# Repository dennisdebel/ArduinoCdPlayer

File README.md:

# Arduino CD player

Using an Arduino Pro-mini and an IDE CD-ROM drive to create a standalone CD player.
Based on the [ATAPIDUINO](http://singlevalve.web.fc2.com/Atapiduino/atapiduino.htm) project - code for this in the `original` folder.

For more details, see project on [hackaday.io](https://hackaday.io/project/176545-arduino-cd-player).

# To do
* Add opamp buffer after DAC to protect the output (from accidental plugging in other outputs).

# Supported IDE CD-ROM drives
Sources from [ATAPIDUINO](http://singlevalve.web.fc2.com/Atapiduino/atapiduino.htm) and [ArduinoCdPlayer](https://hackaday.io/project/176545-arduino-cd-player) and [here](https://hackaday.io/project/24905-using-old-cd-drive-as-a-music-player):

## Testing
* AOpen CRW5224 (2003)

## Compatible drives
* AZTECH CDA66801I (1995)
* BTC F563E (2001)
* CREATIVE CD5233E (?) (Starts PLAY instead of remaining paused when NEXT/PREV is used on stopped unit)
* HITACHI CDR-8130 (1997)
* HITACHI CDR-8230 (1997)
* LG CRD-8320B (1998)
* LG CRD-8322B (1999)
* LG CRD-8521B (2001)
* LG GCE-8527B (2005)
* LITE-ON LTN-403L (2000)
* LITE-ON LTN486S (2001)
* NEC CDR 1800A (1997)
* NEC DV-5800A (2001) ("DVD-ROM READER")
* SAMSUNG SC-148C (2001)
* SONY CDU5211 (2001)
* TEAC CD-532E (2000)
* TEAC CD-540E (2001)
* Ultima Electronics CHA-50 (????)

## Non Compatible or possible defect Units
* Compaq CRC#D-8241B (1998) (erratic, defect?)
* Compaq CR-588 (1998) (erratic, defect?)
* H.L Datastorage GCR-8481B (2002) (fails init proc.)
* LG DVD-ROM Drive GDR-H30N (2007) (fails init proc.)
* Philips DVDROM DROM6116/34 (2004) (Only reads TOC sometimes)
* Toshiba XM-6402B (1999) (fails init proc.)

# References
* https://hackaday.io/project/176545-arduino-cd-player
* https://hackaday.io/project/24905-using-old-cd-drive-as-a-music-player
* http://singlevalve.web.fc2.com/Atapiduino/atapiduino.htm 
* https://github.com/lmiori92/AtapiduinoSingleChip
* productized version of similar idea: [CD-ROM DVD-ROM IDE ROM Audio Player controller DIY kit ROM to Turntable](https://www.ebay.co.uk/itm/CD-ROM-DVD-ROM-IDE-ROM-Audio-Player-controller-DIY-kit-ROM-to-Turntable/324207457799)

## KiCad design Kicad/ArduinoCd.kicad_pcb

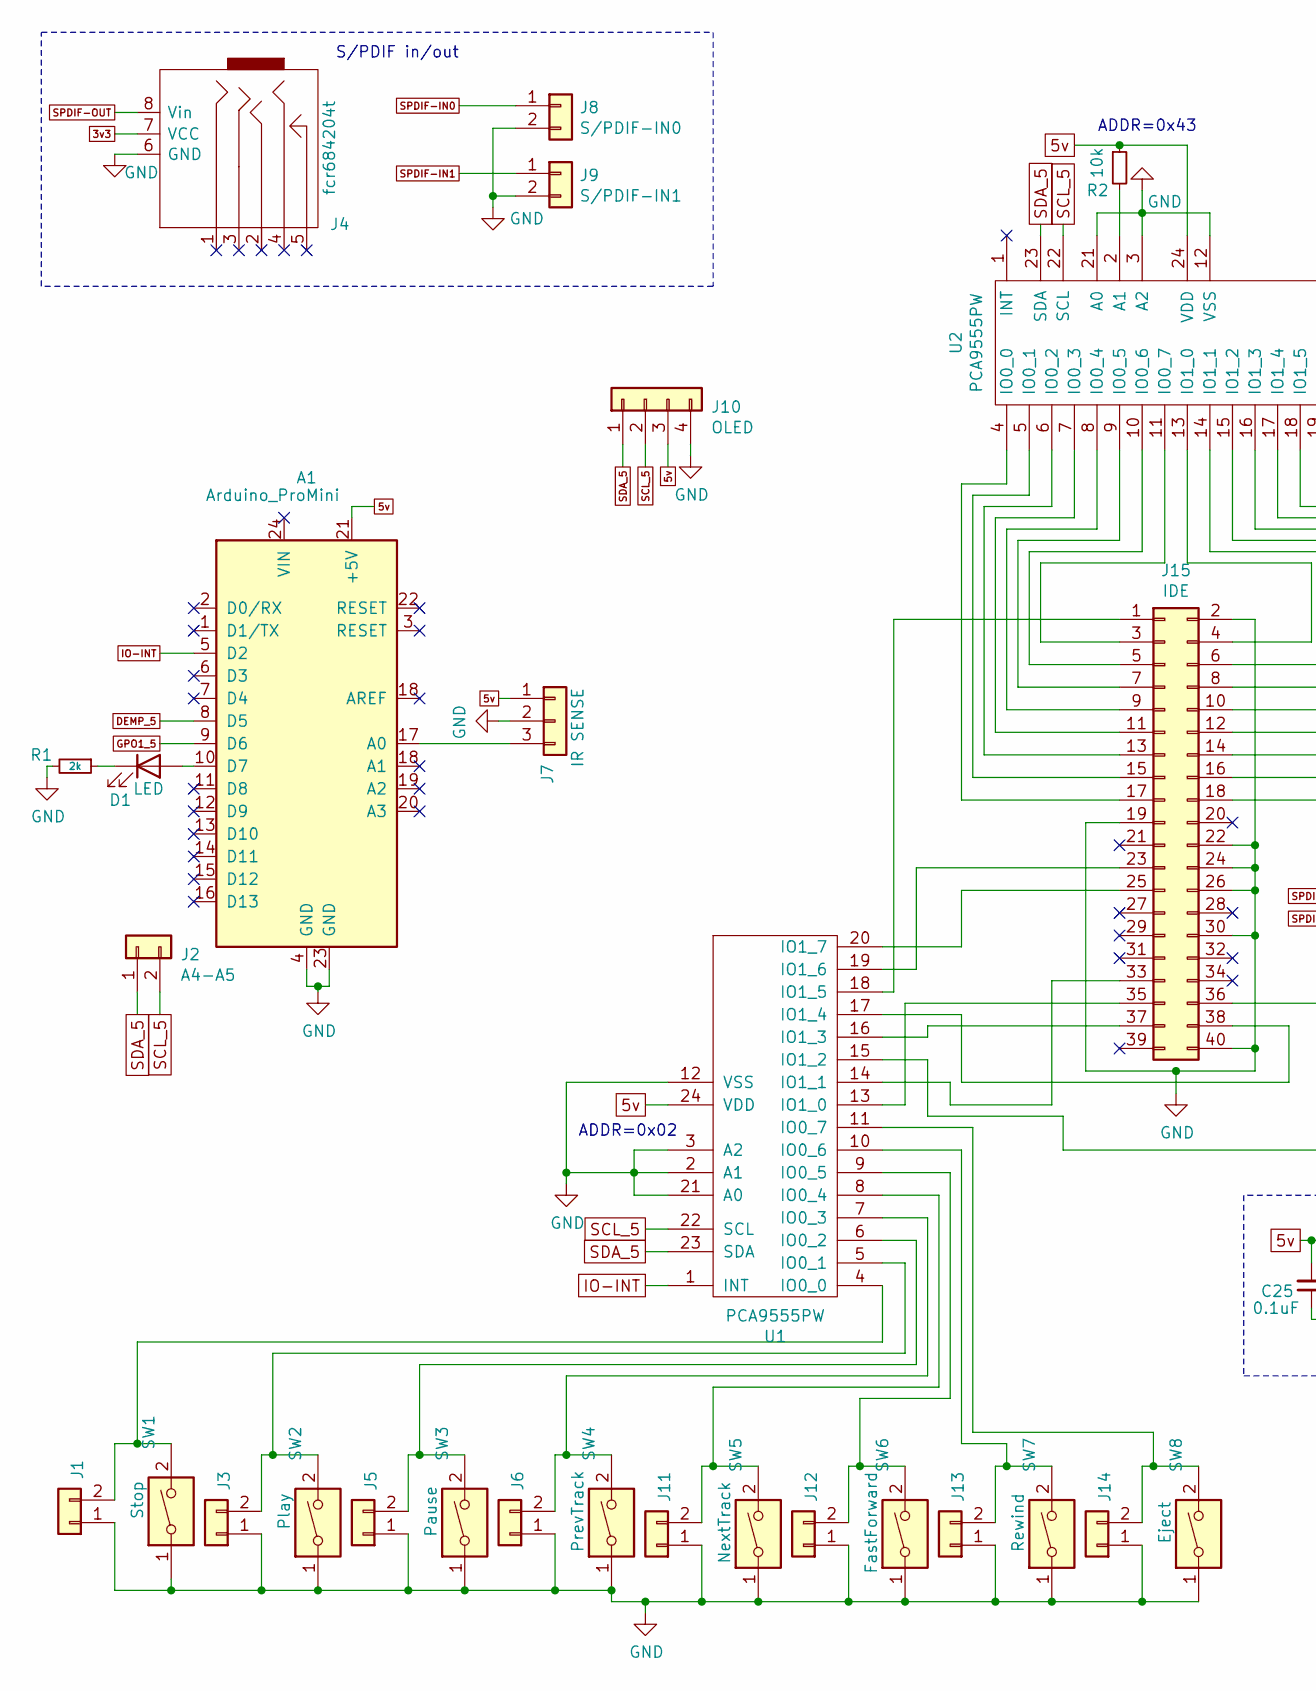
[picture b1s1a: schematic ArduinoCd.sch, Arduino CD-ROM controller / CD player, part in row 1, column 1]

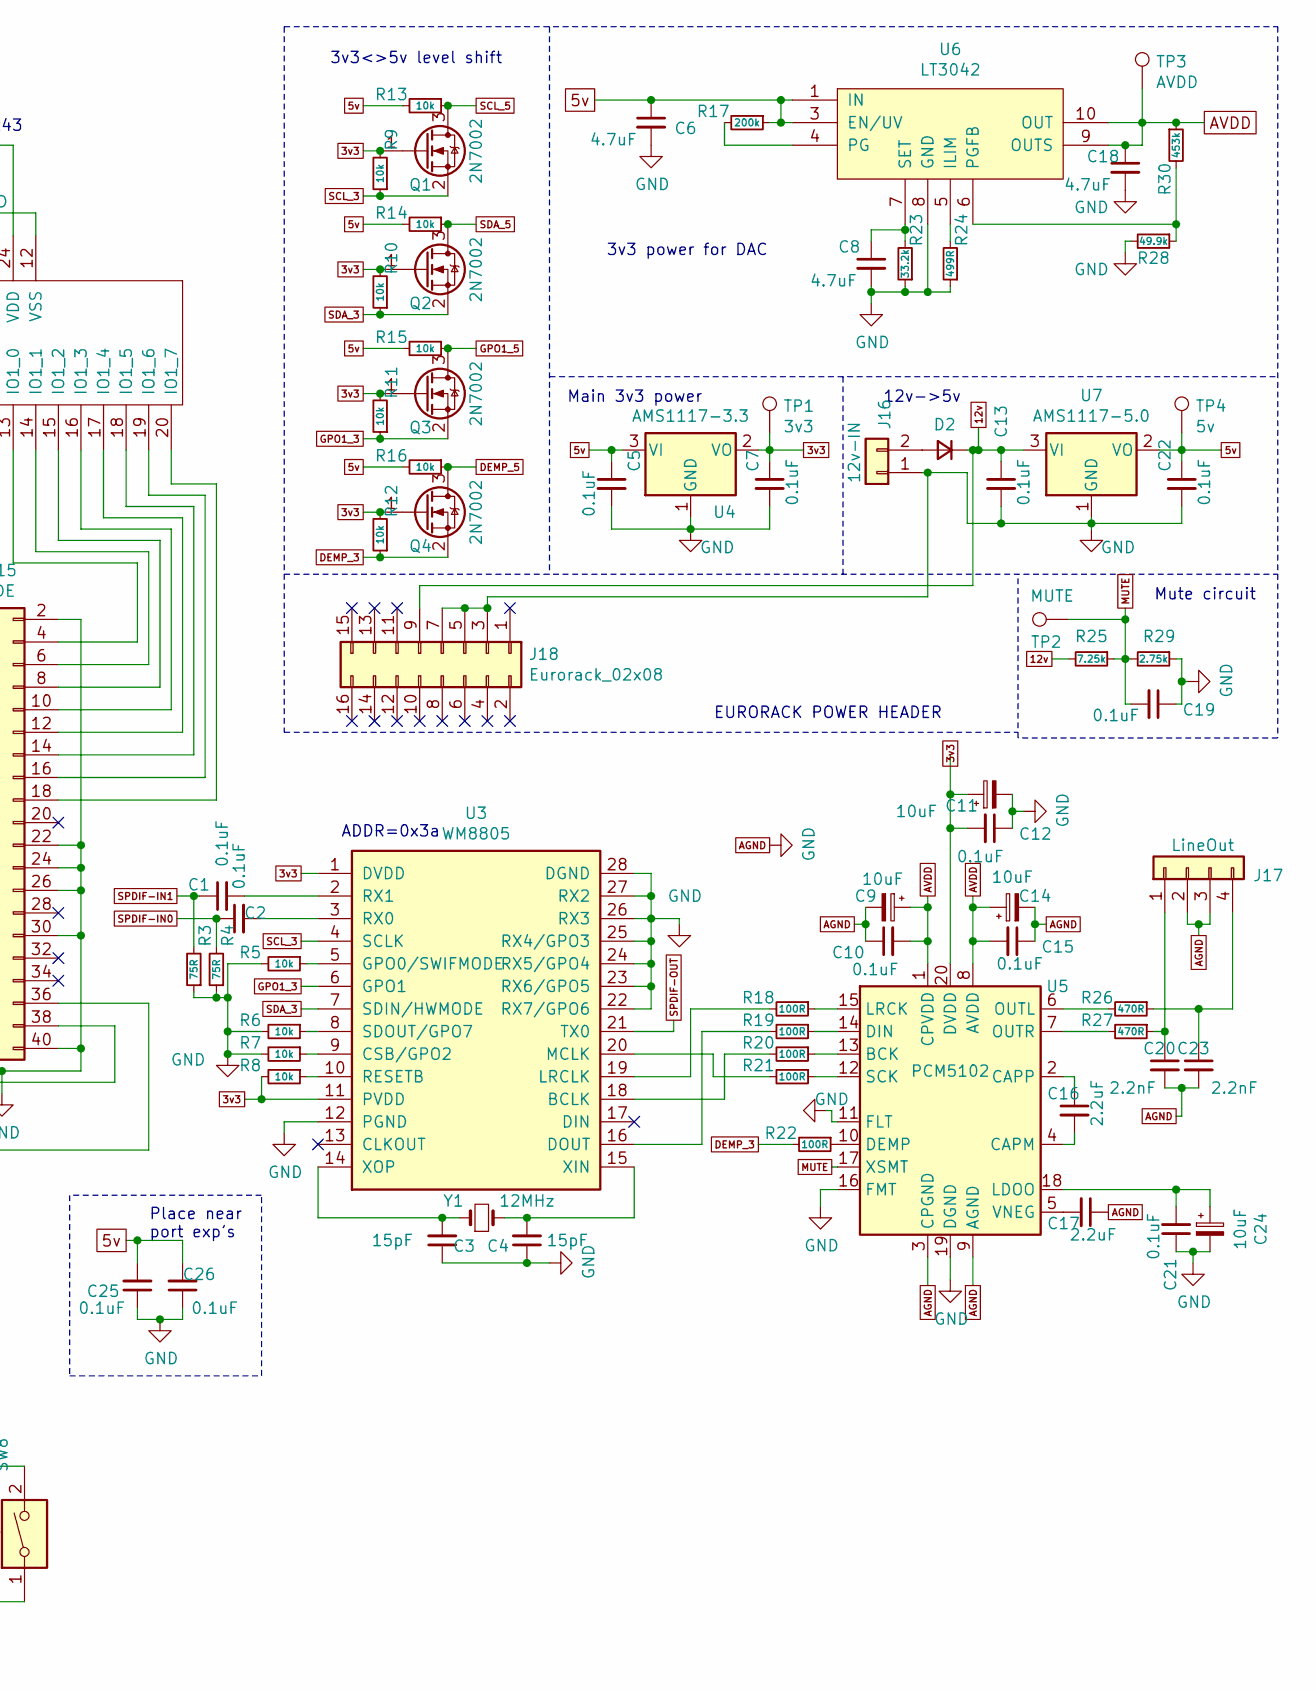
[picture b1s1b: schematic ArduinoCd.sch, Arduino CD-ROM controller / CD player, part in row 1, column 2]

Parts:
A1: Arduino_ProMini
C1, C2, C5, C7, C10, C12, C13, C15, C19, C21, C22, C25, C26: 0.1uF; C_0805_2012Metric_Pad1.15x1.40mm_HandSolder
C3, C4: 15pF; C_0805_2012Metric_Pad1.15x1.40mm_HandSolder
C6, C8, C18: 4.7uF; C_0805_2012Metric_Pad1.15x1.40mm_HandSolder
C9, C11, C14, C24: 10uF; C_0805_2012Metric_Pad1.15x1.40mm_HandSolder
C16, C17: 2.2uF; C_0805_2012Metric_Pad1.15x1.40mm_HandSolder
C20, C23: 2.2nF; C_0805_2012Metric_Pad1.15x1.40mm_HandSolder
D1: LED; LED_D3.0mm
D2: D_Small; D_SMB_Handsoldering
J1, J3, J5, J6, J11, J12, J13, J14: Conn_01x02; PinHeader_1x02_P2.54mm_Vertical
J2: A4-A5; PinHeader_1x02_P2.54mm_Vertical
J4: fcr684204t; FCR684204T
J7: IR SENSE; PinHeader_1x03_P2.54mm_Vertical
J8: S/PDIF-IN0; PinHeader_1x02_P2.54mm_Vertical
J9: S/PDIF-IN1; PinHeader_1x02_P2.54mm_Vertical
J10: OLED; PinHeader_1x04_P2.54mm_Vertical
J15: IDE; PinHeader_2x20_P2.54mm_Vertical
J16: 12v-IN; PinHeader_1x02_P2.54mm_Vertical
J17: LineOut; PinHeader_1x04_P2.54mm_Vertical
J18: Eurorack_02x08; PinHeader_2x08_P2.54mm_Vertical
Q1, Q2, Q3, Q4: 2N7002; SOT-23_Handsoldering
R1: 2k; R_0805_2012Metric_Pad1.15x1.40mm_HandSolder
R2, R5, R6, R7, R8, R9, R10, R11, R12, R13, R14, R15, R16: 10k; R_0805_2012Metric_Pad1.15x1.40mm_HandSolder
R3, R4: 75R; R_0805_2012Metric_Pad1.15x1.40mm_HandSolder
R17: 200k; R_0805_2012Metric_Pad1.15x1.40mm_HandSolder
R18, R19, R20, R21, R22: 100R; R_0805_2012Metric_Pad1.15x1.40mm_HandSolder
R23: 33.2k; R_0805_2012Metric_Pad1.15x1.40mm_HandSolder
R24: 499R; R_0805_2012Metric_Pad1.15x1.40mm_HandSolder
R25: 7.25k; R_0805_2012Metric_Pad1.15x1.40mm_HandSolder
R26, R27: 470R; R_0805_2012Metric_Pad1.15x1.40mm_HandSolder
R28: 49.9k; R_0805_2012Metric_Pad1.15x1.40mm_HandSolder
R29: 2.75k; R_0805_2012Metric_Pad1.15x1.40mm_HandSolder
R30: 453k; R_0805_2012Metric_Pad1.15x1.40mm_HandSolder
SW1: Stop; SW_SPST_B3S-1000
SW2: Play; SW_SPST_B3S-1000
SW3: Pause; SW_SPST_B3S-1000
SW4: PrevTrack; SW_SPST_B3S-1000
SW5: NextTrack; SW_SPST_B3S-1000
SW6: FastForward; SW_SPST_B3S-1000
SW7: Rewind; SW_SPST_B3S-1000
SW8: Eject; SW_SPST_B3S-1000
TP1: 3v3; TestPoint_Pad_1.0x1.0mm
TP2: MUTE; TestPoint_Pad_1.0x1.0mm
TP3: AVDD; TestPoint_Pad_1.0x1.0mm
TP4: 5v; TestPoint_Pad_1.0x1.0mm
U1, U2: PCA9555PW; TSSOP-24_4.4x7.8mm_P0.65mm
U3: WM8805; SSOP-28_5.3x10.2mm_P0.65mm
U4: AMS1117-3.3; SOT-223-3_TabPin2
U5: PCM5102; TSSOP-20_4.4x6.5mm_P0.65mm
U6: LT3042; MSOP-10_3x3mm_P0.5mm
U7: AMS1117-5.0; SOT-223-3_TabPin2
Y1: 12MHz; Crystal_SMD_HC49-SD

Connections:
3v3: C7.1, C11.1, C12.2, J4.7 (VCC), Q1.1 (G), Q2.1 (G), Q3.1 (G), Q4.1 (G), R8.2, R9.2, R10.2, R11.2, R12.2, TP1.1, U3.1 (DVDD), U3.11 (PVDD), U4.2 (VO), U5.20 (DVDD)
5v: A1.21 (+5V), C5.1, C6.1, C22.1, C25.2, C26.2, J7.1, J10.3, R2.1, R13.2, R14.2, R15.2, R16.2, R17.1, TP4.1, U1.24 (VDD), U2.24 (VDD), U4.3 (VI), U6.1 (IN), U6.2 (IN), U6.3 (EN/UV), U7.2 (VO)
12v: C13.1, D2.1 (K), J18.9, R25.2, U7.3 (VI)
AGND: A1.4 (GND), A1.23 (GND), C3.1, C4.1, C5.2, C6.2, C7.2, C8.2, C9.2, C10.1, C11.2, C12.1, C13.2, C14.2, C15.1, C17.1, C18.2, C19.1, C20.2, C21.1, C22.2, C23.2, C24.2, C25.1, C26.1, J1.1, J3.1, J4.6 (GND), J5.1, J6.1, J7.2, J8.2, J9.2, J10.4, J11.1, J12.1, J13.1, J14.1, J15.2, J15.19, J15.22, J15.24, J15.26, J15.30, J15.40, J16.1, J17.2, J17.3, J18.3, J18.5, J18.7, R1.2, R3.1, R4.1, R5.2, R6.2, R7.2, R23.1, R24.1, R28.2, R29.1, SW1.1, SW2.1, SW3.1, SW4.1, SW5.1, SW6.1, SW7.1, SW8.1, U1.2 (A1), U1.3 (A2), U1.12 (VSS), U1.21 (A0), U2.3 (A2), U2.12 (VSS), U2.21 (A0), U3.12 (PGND), U3.22 (RX7/GPO6), U3.23 (RX6/GPO5), U3.24 (RX5/GPO4), U3.25 (RX4/GPO3), U3.26 (RX3), U3.27 (RX2), U3.28 (DGND), U4.1 (GND), U5.3 (CPGND), U5.9 (AGND), U5.11 (FLT), U5.16 (FMT), U5.19 (DGND), U6.8 (GND), U7.1 (GND)
AVDD: C9.1, C10.2, C14.1, C15.2, C18.1, R30.1, TP3.1, U5.1 (CPVDD), U5.8 (AVDD), U6.9 (OUTS), U6.10 (OUT)
DEMP_3: Q4.2 (S), R12.1, R22.2
DEMP_5: A1.8 (D5), Q4.3 (D), R16.1
GPO1_3: Q3.2 (S), R11.1, U3.6 (GPO1)
GPO1_5: A1.9 (D6), Q3.3 (D), R15.1
IO-INT: A1.5 (D2), U1.1 (INT)
MUTE: C19.2, R25.1, R29.2, TP2.1, U5.17 (XSMT)
unnamed: A1.10 (D7), D1.2 (A)
unnamed: A1.17 (A0), J7.3
unnamed: C1.2, U3.2 (RX1)
unnamed: C2.2, U3.3 (RX0)
unnamed: C3.2, U3.14 (XOP), Y1.1
unnamed: C4.2, U3.15 (XIN), Y1.2
unnamed: C8.1, R23.2, U6.7 (SET)
unnamed: C16.1, U5.2 (CAPP)
unnamed: C16.2, U5.4 (CAPM)
unnamed: C17.2, U5.5 (VNEG)
unnamed: C20.1, J17.1, R27.1
unnamed: C21.2, C24.1, U5.18 (LDOO)
unnamed: C23.1, J17.4, R26.1
unnamed: D1.1 (K), R1.1
unnamed: D2.2 (A), J16.2
unnamed: J1.2, SW1.2, U1.4 (IO0_0)
unnamed: J3.2, SW2.2, U1.5 (IO0_1)
unnamed: J5.2, SW3.2, U1.6 (IO0_2)
unnamed: J6.2, SW4.2, U1.7 (IO0_3)
unnamed: J11.2, SW5.2, U1.8 (IO0_4)
unnamed: J12.2, SW6.2, U1.9 (IO0_5)
unnamed: J13.2, SW7.2, U1.10 (IO0_6)
unnamed: J14.2, SW8.2, U1.11 (IO0_7)
unnamed: J15.1, U1.18 (IO1_5)
unnamed: J15.3, U2.11 (IO0_7)
unnamed: J15.4, U2.13 (IO1_0)
unnamed: J15.5, U2.10 (IO0_6)
unnamed: J15.6, U2.14 (IO1_1)
unnamed: J15.7, U2.9 (IO0_5)
unnamed: J15.8, U2.15 (IO1_2)
unnamed: J15.9, U2.8 (IO0_4)
unnamed: J15.10, U2.16 (IO1_3)
unnamed: J15.11, U2.7 (IO0_3)
unnamed: J15.12, U2.17 (IO1_4)
unnamed: J15.13, U2.6 (IO0_2)
unnamed: J15.14, U2.18 (IO1_5)
unnamed: J15.15, U2.5 (IO0_1)
unnamed: J15.16, U2.19 (IO1_6)
unnamed: J15.17, U2.4 (IO0_0)
unnamed: J15.18, U2.20 (IO1_7)
unnamed: J15.23, U1.19 (IO1_6)
unnamed: J15.25, U1.20 (IO1_7)
unnamed: J15.33, U1.14 (IO1_1)
unnamed: J15.35, U1.13 (IO1_0)
unnamed: J15.36, U1.15 (IO1_2)
unnamed: J15.37, U1.16 (IO1_3)
unnamed: J15.38, U1.17 (IO1_4)
unnamed: R2.2, U2.2 (A1)
unnamed: R5.1, U3.5 (GPO0/SWIFMODE)
unnamed: R6.1, U3.8 (SDOUT/GPO7)
unnamed: R7.1, U3.9 (CSB/GPO2)
unnamed: R8.1, U3.10 (RESETB)
unnamed: R17.2, U6.4 (PG)
unnamed: R18.1, U5.15 (LRCK)
unnamed: R18.2, U3.19 (LRCLK)
unnamed: R19.1, U5.14 (DIN)
unnamed: R19.2, U3.16 (DOUT)
unnamed: R20.1, U5.13 (BCK)
unnamed: R20.2, U3.18 (BCLK)
unnamed: R21.1, U5.12 (SCK)
unnamed: R21.2, U3.20 (MCLK)
unnamed: R22.1, U5.10 (DEMP)
unnamed: R24.2, U6.5 (ILIM)
unnamed: R26.2, U5.6 (OUTL)
unnamed: R27.2, U5.7 (OUTR)
unnamed: R28.1, R30.2, U6.6 (PGFB)
SCL_3: Q1.2 (S), R9.1, U3.4 (SCLK)
SCL_5: J2.2, J10.2, Q1.3 (D), R13.1, U1.22 (SCL), U2.22 (SCL)
SDA_3: Q2.2 (S), R10.1, U3.7 (SDIN/HWMODE)
SDA_5: J2.1, J10.1, Q2.3 (D), R14.1, U1.23 (SDA), U2.23 (SDA)
SPDIF-IN0: C2.1, J8.1, R4.2
SPDIF-IN1: C1.1, J9.1, R3.2
SPDIF-OUT: J4.8 (Vin), U3.21 (TX0)

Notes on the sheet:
ADDR=0x02
ADDR=0x43
3v3 power for DAC
3v3<>5v level shift
ADDR=0x3a
Main 3v3 power
12v->5v
Mute circuit
Place near port exp's
EURORACK POWER HEADER
S/PDIF in/out

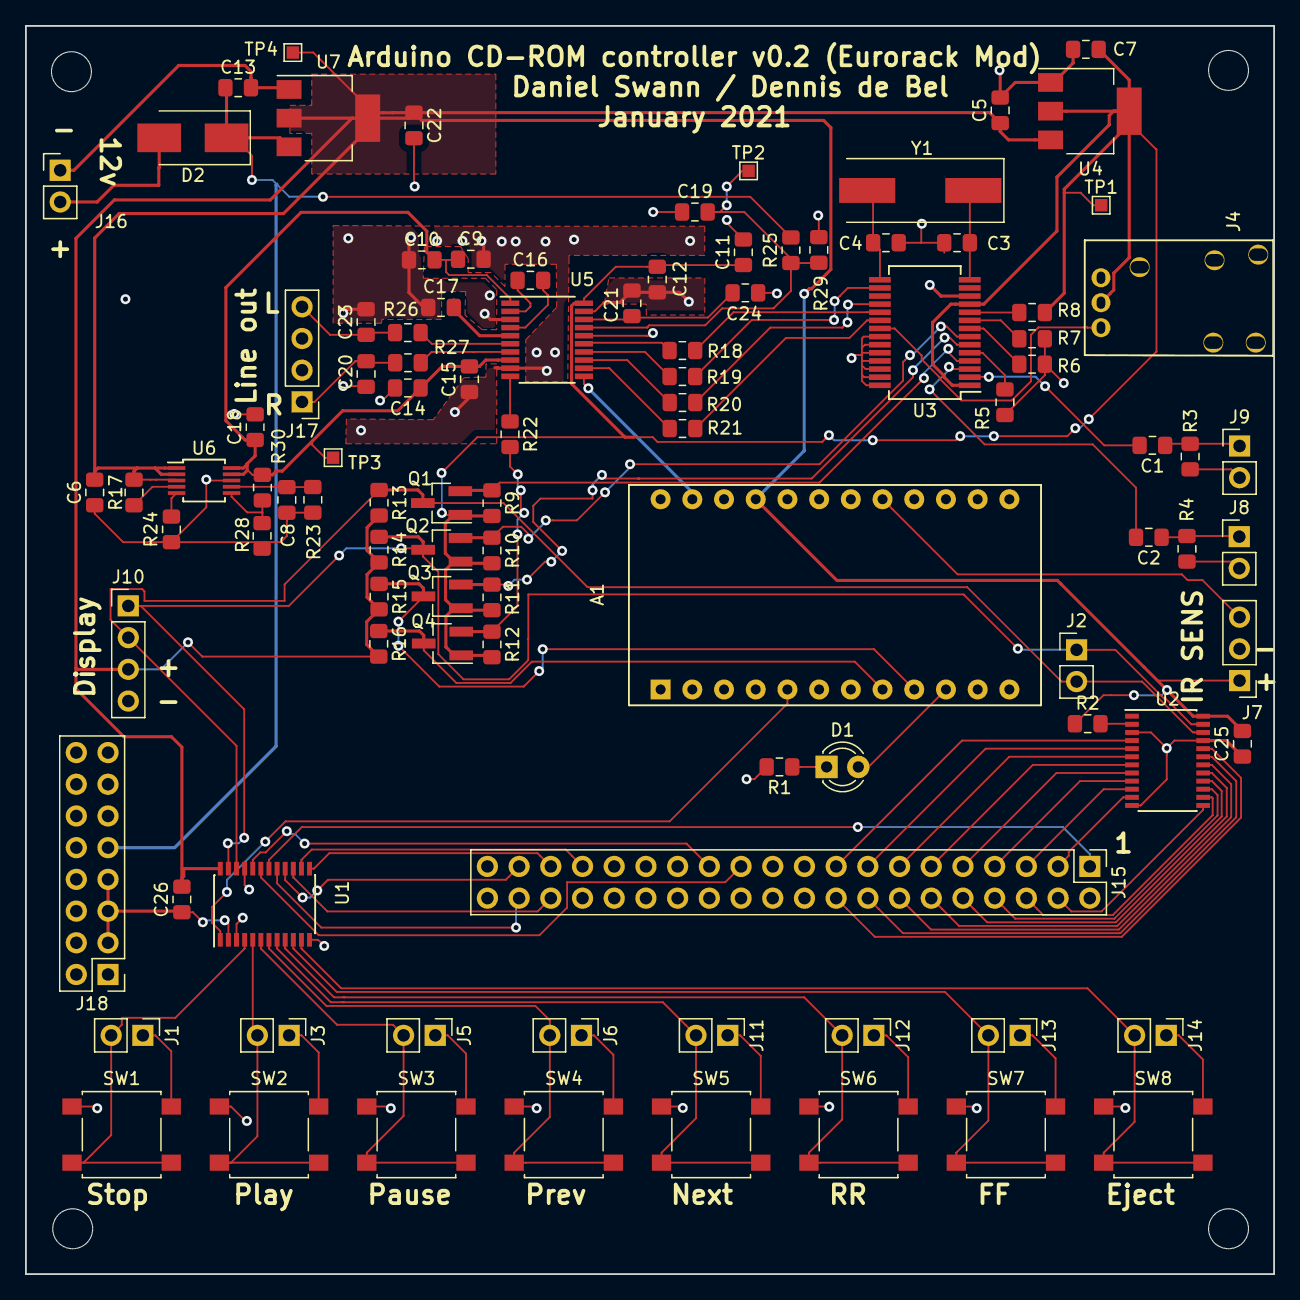
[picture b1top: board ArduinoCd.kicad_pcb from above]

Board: 2 copper layers, 100.0 x 100.0 mm, 101 parts (0 on the bottom side), 84 nets.

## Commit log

2021-01-12 started list of compatible drives
    Collected from various references, more to come when I actually get this working
2021-01-12 added more refs
2021-01-12 fixed link
2021-01-12 added more testing models
2021-01-16 added tested cdrom drives
    and alphabetically sorted the list of devices
2021-01-29 renamed few folders for clarity, unzipped kicad files for Diffing purposes
2021-01-29 added my version of pcb (includes power connector and bodge wire fix, but wm8805 doesnt work)
2021-03-04 Update README.md
    moved philips dvd drive to incompatible drives
